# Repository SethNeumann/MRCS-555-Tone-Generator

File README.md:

# REPO NAME: MRCS-555-Tone-Generator

## License: Creative Commons Attribution-NonCommercial-ShareAlike

This board uses the popular NE555 as an Astable Multivibrator to create an audio frquency square wave.  When operated at 5V it can drive a speaker quite hard,
volume can be increased by increasing supply voltage.  A pot it included to change the frequency over a range of lll to hhh.  This circuit is derived from the
555 applilcation notes and take features from a number of popular designs on the internet.

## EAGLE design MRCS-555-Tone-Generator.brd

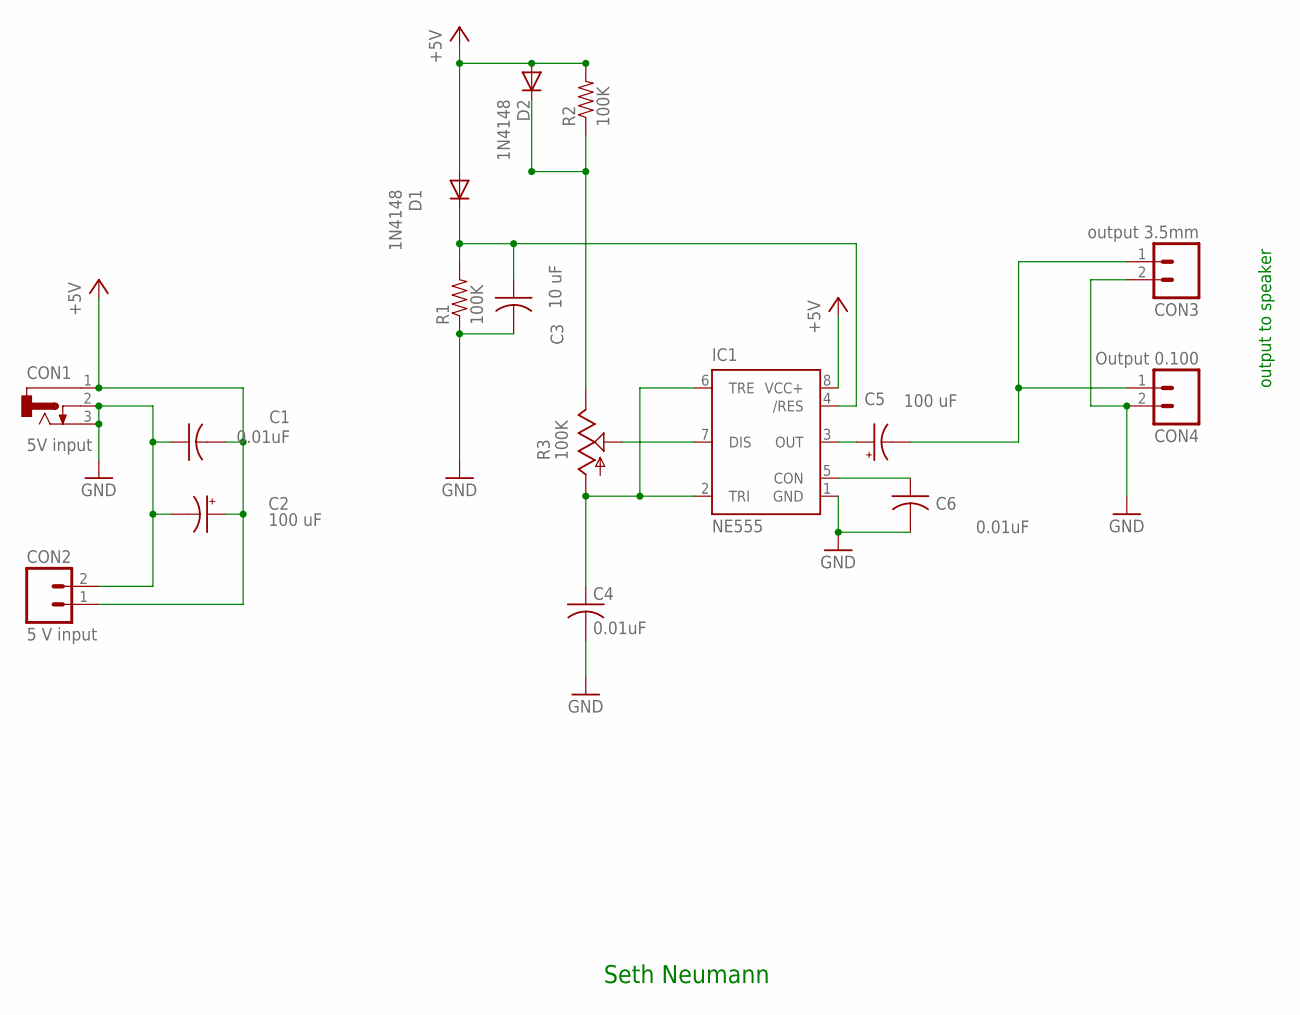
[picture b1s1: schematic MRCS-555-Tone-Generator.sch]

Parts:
C1, C4, C6: 0.01uF; C-PTH-0.100
C2, C5: 100 uF; E3.5-10
C3: 10 uF; C-PTH-0.100
CON1: 5V input; DCJ0202
CON2: 5 V input; 1X02_LOCK
CON3: output 3.5mm; SCREWTERMINAL-3.5MM-2_LOCK
CON4: Output 0.100; 1X02_LOCK
D1, D2: 1N4148; DIODE-1N4148
IC1: NE555; DIL-08
R1, R2: 100K; AXIAL-0.4-RES
R3: 100K; RS3

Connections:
+5V: C1.2, C2.+, CON1.1, CON2.1 (A), D1.A, D2.A, IC1.8 (VCC+), R2.P$2 (2)
GND: C1.1, C2.-, C3.2, C4.2, C6.2, CON1.2, CON1.3, CON2.2 (B), CON3.2 (B), CON4.2 (B), IC1.1 (GND), R1.P$1 (1)
unnamed: C5.-, CON3.1 (A), CON4.1 (A)
unnamed: C6.1, IC1.5 (CON)
unnamed: C5.+, IC1.3 (OUT)
unnamed: C4.1, IC1.2 (TRI), IC1.6 (TRE), R3.A
unnamed: D2.C, R2.P$1 (1), R3.E
unnamed: C3.1, D1.C, IC1.4 (/RES), R1.P$2 (2)
unnamed: IC1.7 (DIS), R3.S

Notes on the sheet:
output to speaker
Seth Neumann

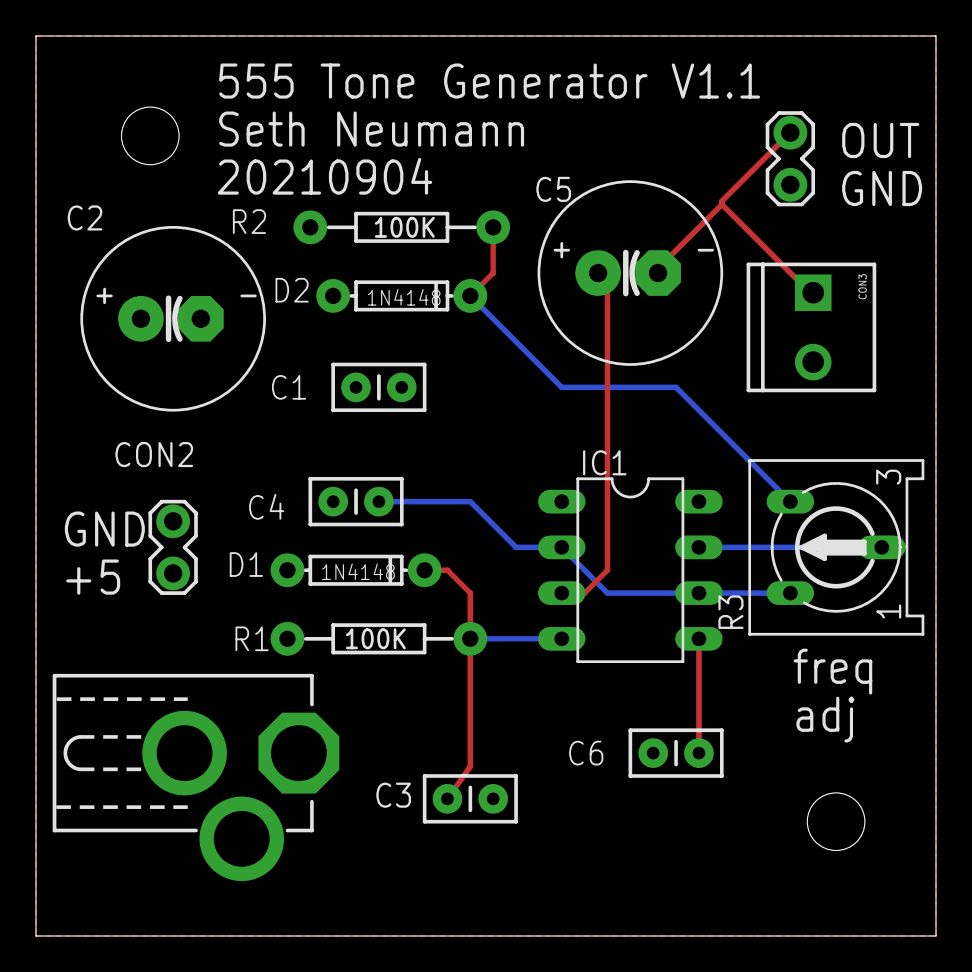
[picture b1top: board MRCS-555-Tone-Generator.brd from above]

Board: 2 copper layers, 50.0 x 50.0 mm, 19 parts (0 on the bottom side), 9 nets.

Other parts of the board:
U$1: MRCSLOGOTOP
U$2: MRCSLOGOBTM
U$3: CA-PROP65WARNING

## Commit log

2021-08-28 Update DESCRIPTION
2021-08-28 intialcommit
2021-08-28 finish moving initial design files into Github
2021-09-04 Updates after first article tested good
    clean up of some nomenclature
2021-09-04 changes to show production status
    cleaned up some nomenclature and showed product in production
2021-09-04 Minor updates after building 1st articles
    Changed C3 from electrolytic to 0.1 for Tant or Monolithic
    Minor clean up of labels on board
